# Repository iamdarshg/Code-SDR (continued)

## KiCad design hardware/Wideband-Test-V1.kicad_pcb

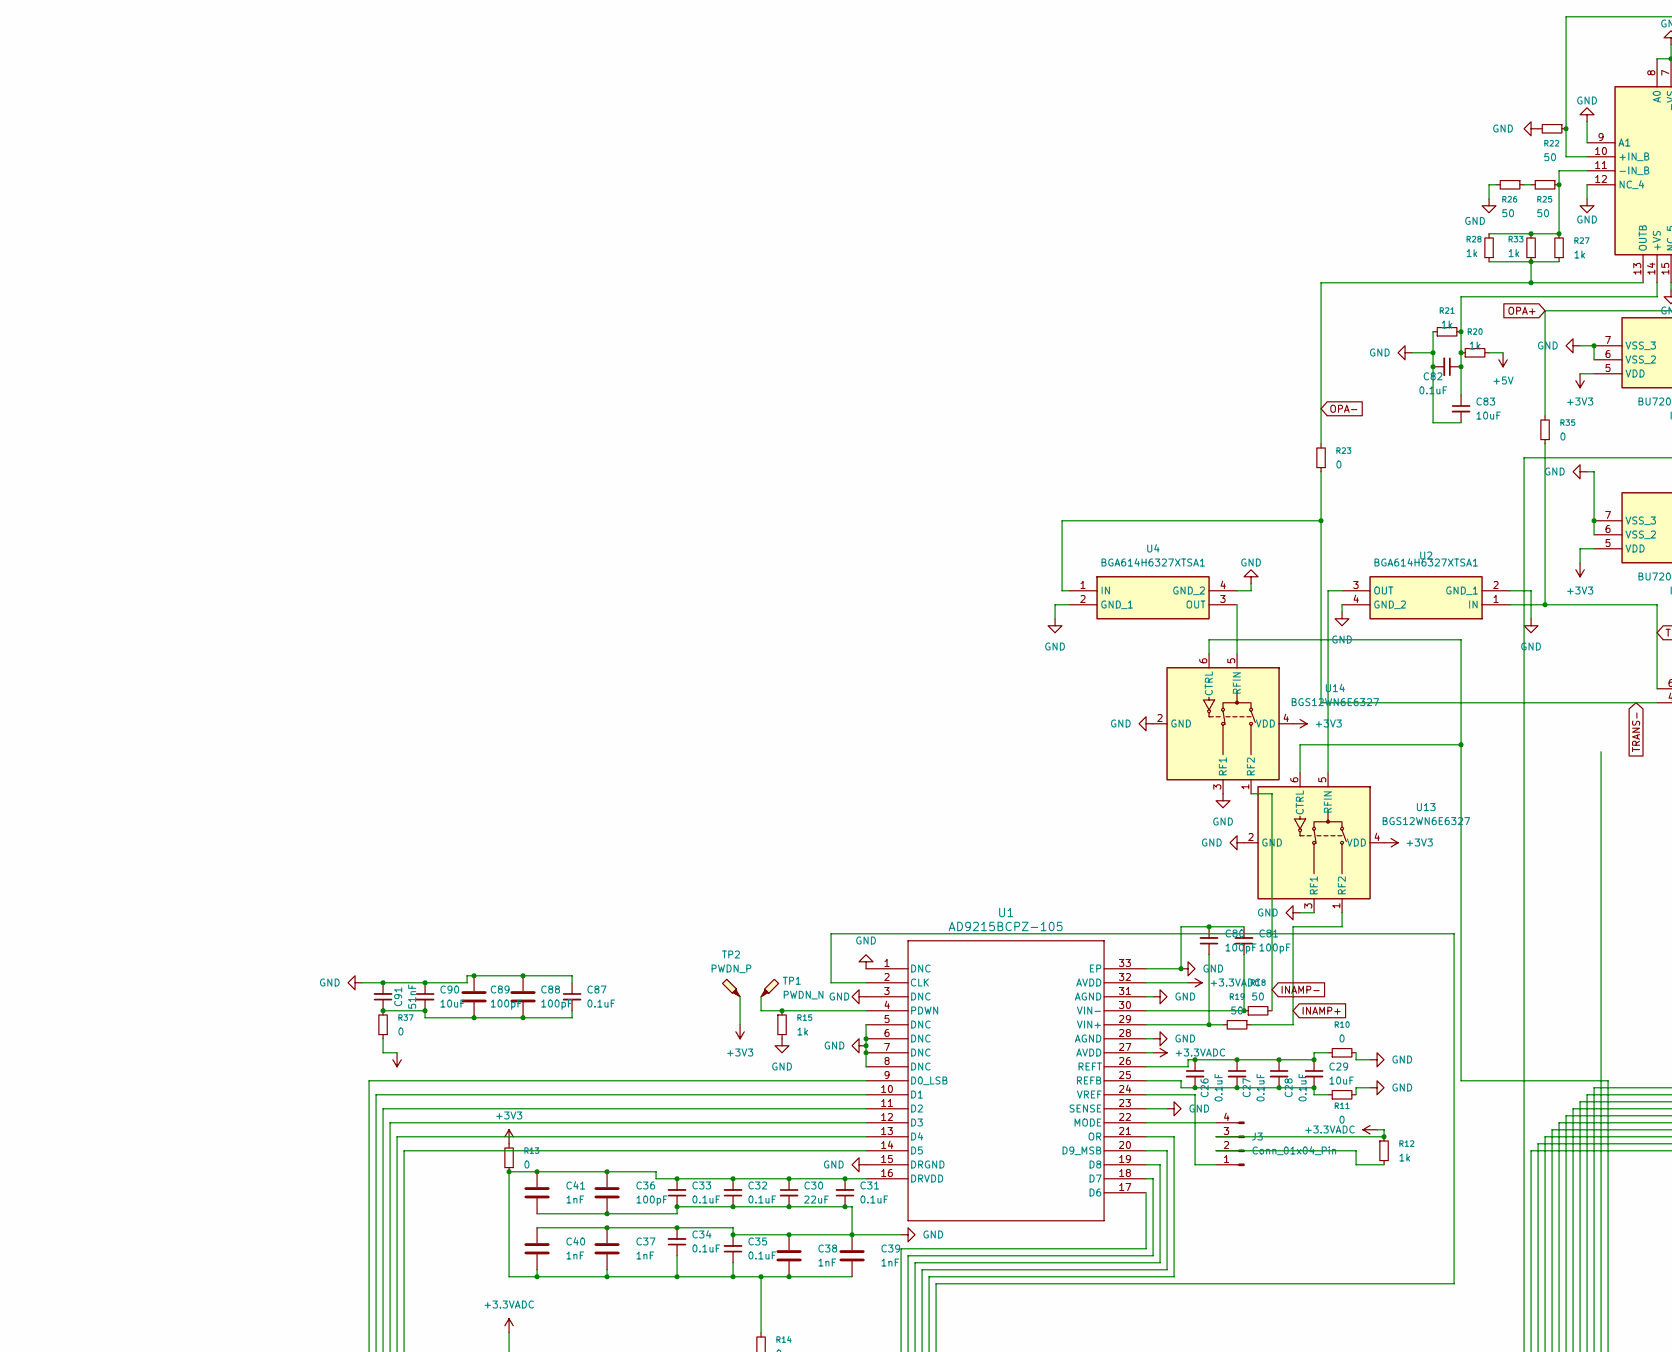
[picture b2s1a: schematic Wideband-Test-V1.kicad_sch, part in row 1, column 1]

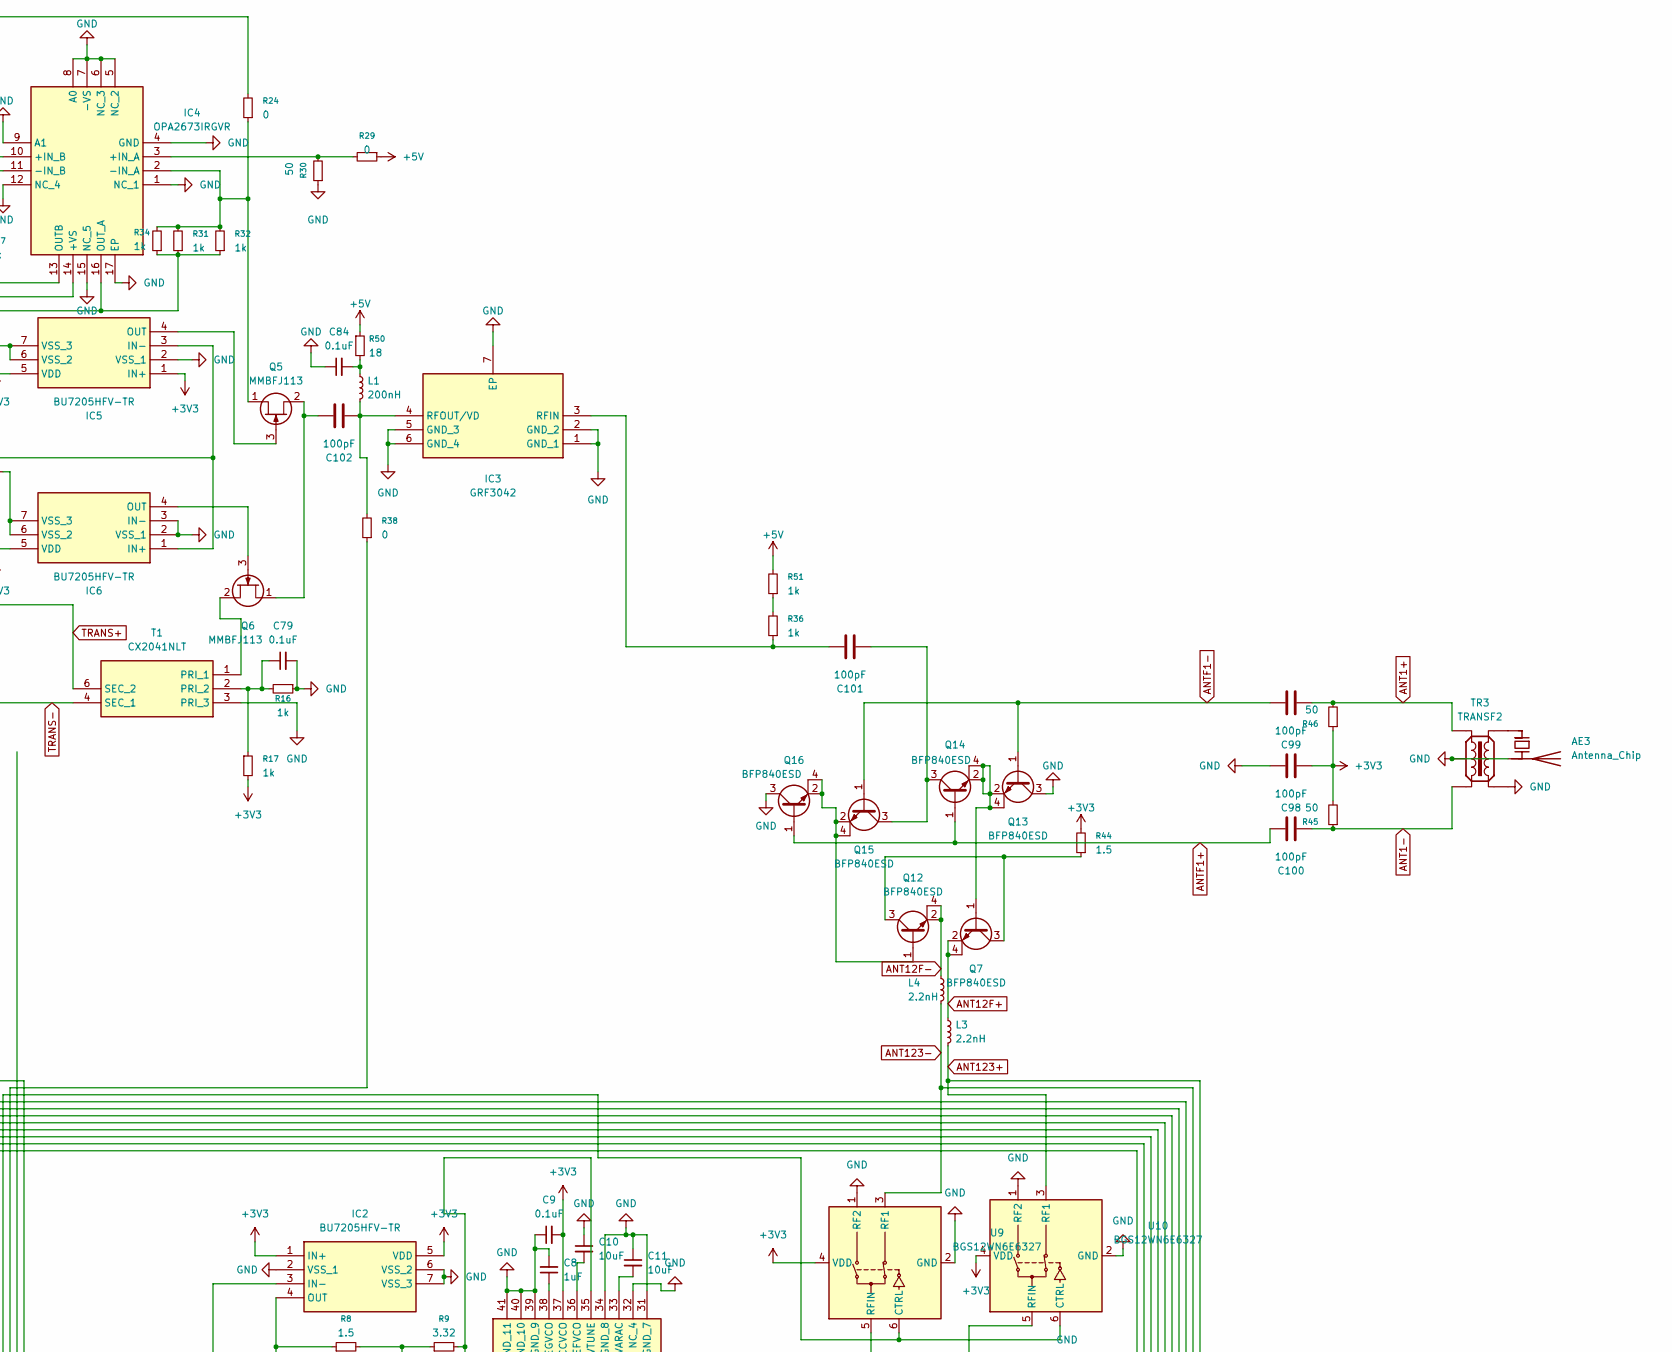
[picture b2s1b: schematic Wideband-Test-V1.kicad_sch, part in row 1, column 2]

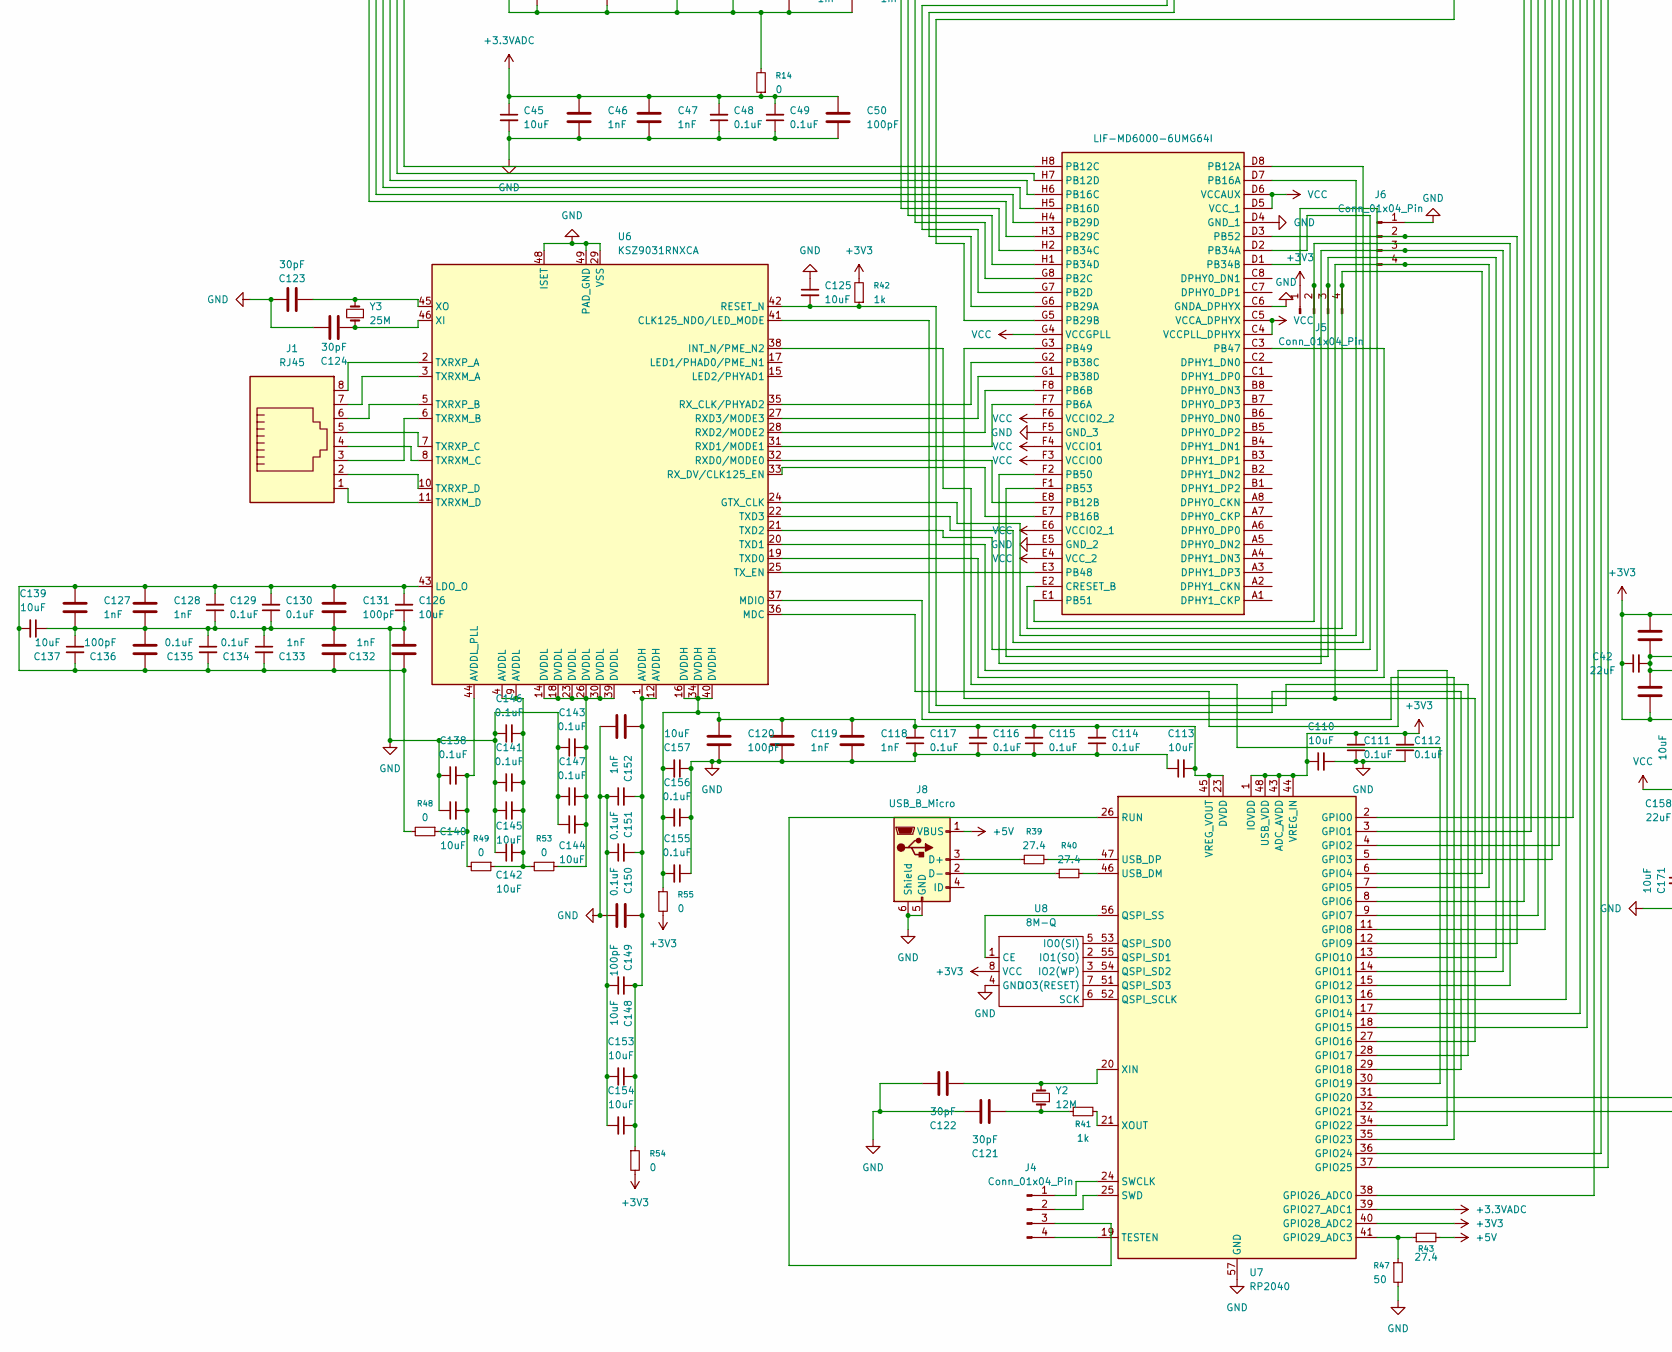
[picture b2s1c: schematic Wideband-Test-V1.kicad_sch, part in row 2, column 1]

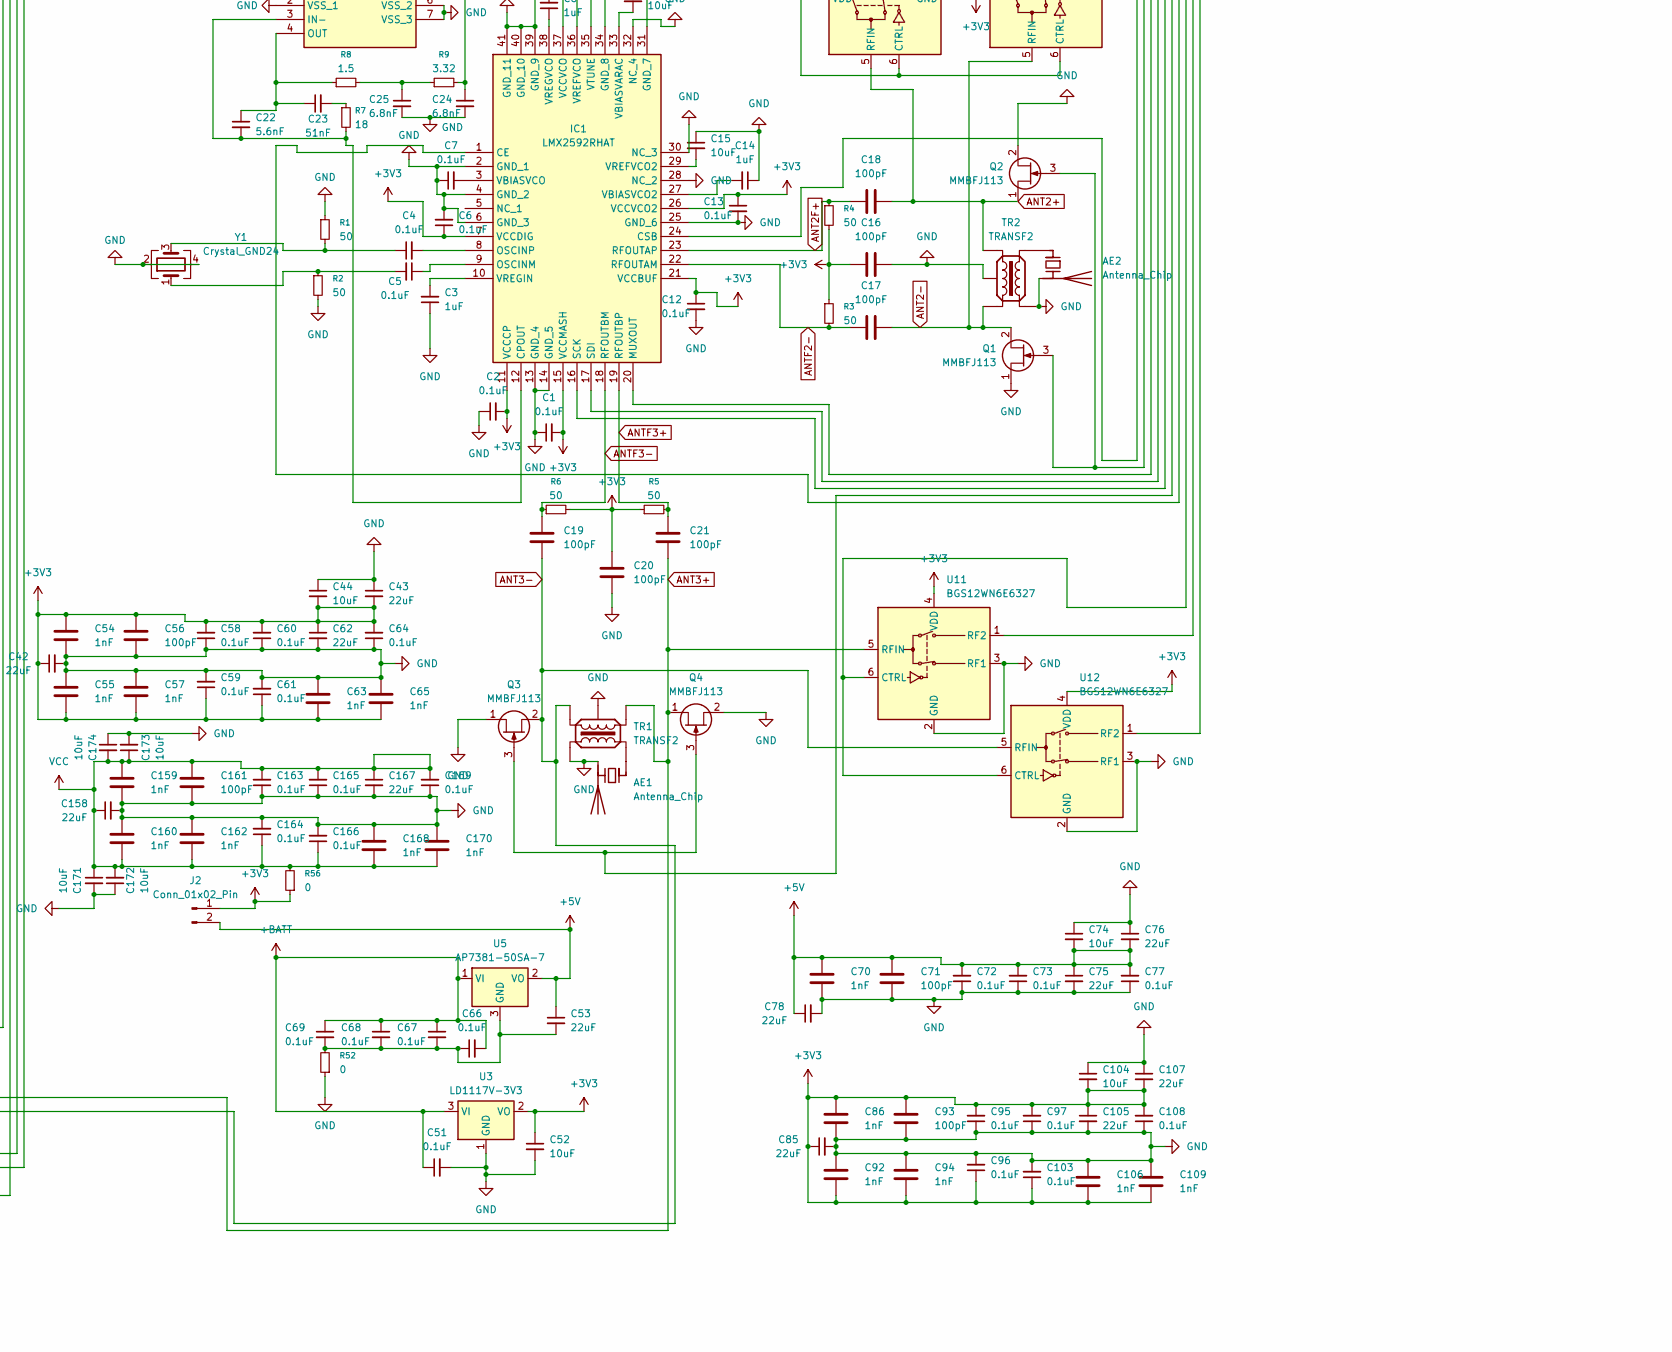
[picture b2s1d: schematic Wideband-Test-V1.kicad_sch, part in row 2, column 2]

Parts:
AE1, AE2, AE3: Antenna_Chip; SMA_Molex_73251-2200_Horizontal
C1, C2, C4, C5, C6, C7, C9, C12, C13, C26, C27, C28, C31, C32, C33, C34, C35, C48, C49, C51, C58, C59, C60, C61, C64, C66, C67, C68, C69, C72, C73, C77, C79, C82, C84, C87, C95, C96, C97, C103, C108, C111, C112, C114, C115, C116, C117, C129, C130, C134, C135, C138, C141, C143, C146, C147, C150, C151, C155, C156, C163, C164, C165, C166, C169: 0.1uF; C_0603_1608Metric
C3, C8, C14: 1uF; C_0805_2012Metric
C10, C11, C15, C29, C44, C45, C52, C74, C83, C90, C104, C110, C113, C125, C126, C137, C139, C140, C142, C144, C145, C148, C153, C154, C157, C171, C172, C173, C174: 10uF; C_0603_1608Metric
C16, C17, C18, C19, C20, C21, C36, C50, C56, C71, C88, C89, C93, C98, C99, C100, C101, C102, C120, C131, C136, C149, C161: 100pF; C_0603_1608Metric
C22: 5.6nF; C_0402_1005Metric
C23, C91: 51nF; C_1206_3216Metric
C24, C25: 6.8nF; C_0402_1005Metric
C30, C42, C43, C53, C62, C75, C76, C78, C85, C105, C107, C158, C167: 22uF; C_1206_3216Metric
C37, C38, C39, C40, C41, C46, C47, C54, C55, C57, C63, C65, C70, C86, C92, C94, C106, C109, C118, C119, C127, C128, C132, C133, C152, C159, C160, C162, C168, C170: 1nF; C_0402_1005Metric
C80, C81: 100pF; C_0402_1005Metric
C121, C122, C123, C124: 30pF; C_0603_1608Metric
IC1: LMX2592RHAT; VQFN-40-1EP_6x6mm_P0.5mm_EP3.5x3.5mm_ThermalVias; Manufacturer_Part_Number LMX2592RHAT; Mouser Part Number 595-LMX2592RHAT
IC2, IC5, IC6: BU7205HFV-TR; HVSOF5; Manufacturer_Part_Number BU7205HFV-TR; Mouser Part Number 755-BU7205HFV-TR
IC3: GRF3042; Renesas_DFN-6_1.5x1.6mm_P0.5mm; Manufacturer_Part_Number GRF3042; Mouser Part Number 459-GRF3042
IC4: OPA2673IRGVR; QFN-16-1EP_4x4mm_P0.65mm_EP2.1x2.1mm_ThermalVias; Manufacturer_Part_Number OPA2673IRGVR; Mouser Part Number 595-OPA2673IRGVR
IC7: LIF-MD6000-6UMG64I; BGA64C40P8X8_350X350X100; Manufacturer_Part_Number LIF-MD6000-6UMG64I; Mouser Part Number 842-LIFMD60006UMG64I
J1: RJ45; RJ45_Amphenol_54602-x08_Horizontal
J2: Conn_01x02_Pin; JWT_A3963_1x02_P3.96mm_Vertical
J3: Conn_01x04_Pin; Molex_Micro-Fit_3.0_43045-0412_2x02_P3.00mm_Vertical
J4, J5, J6: Conn_01x04_Pin; PinHeader_1x04_P2.54mm_Vertical
J8: USB_B_Micro; USB_Micro-B_Amphenol_10118193-0001LF_Horizontal
L1: 200nH; L_0402_1005Metric
L3, L4: 2.2nH; L_0603_1608Metric
Q1, Q2, Q3, Q4, Q5, Q6: MMBFJ113; Diodes_DFN1006-3
Q7, Q12, Q13, Q14, Q15, Q16: BFP840ESD; SOT-343_SC-70-4
R1, R2, R3, R4, R5, R6, R18, R19, R22, R25, R26, R30, R45, R46, R47: 50; R_0201_0603Metric
R7, R50: 18; R_0805_2012Metric
R8, R44: 1.5; R_0603_1608Metric
R9: 3.32; R_0603_1608Metric
R10, R11, R13, R14, R23, R24, R29, R35, R37, R38, R48, R49, R52, R53, R54, R55, R56: 0; R_0603_1608Metric
R12, R15, R16, R17, R20, R21, R27, R28, R31, R32, R33, R34, R36, R41, R42, R51: 1k; R_0805_2012Metric
R39, R40, R43: 27.4; R_0402_1005Metric
T1: CX2041NLT; Filter_SAW-6_3.8x3.8mm; Manufacturer_Part_Number CX2041NLT; Mouser Part Number 673-CX2041NLT
TP1: PWDN_N; PinHeader_1x01_P2.54mm_Vertical
TP2: PWDN_P; PinHeader_1x01_P2.54mm_Vertical
TR1, TR2, TR3: TRANSF2; MABA011108
U1: AD9215BCPZ-105; LFCSP-32-1EP_5x5mm_P0.5mm_EP3.6x3.6mm_ThermalVias
U2, U4: BGA614H6327XTSA1; SOT-343_SC-70-4; Manufacturer_Part_Number BGA614H6327XTSA1; Mouser Part Number 726-BGA614H6327XTSA1
U3: LD1117V-3V3; TO-220-3_Vertical
U5: AP7381-50SA-7; SOT-23
U6: KSZ9031RNXCA; QFN-48-1EP_7x7mm_P0.5mm_EP5.15x5.15mm_ThermalVias
U7: RP2040; QFN-56-1EP_7x7mm_P0.4mm_EP3.2x3.2mm_ThermalVias
U8: 8M-Q; SOIC-8_5.3x5.3mm_P1.27mm
U9, U10, U11, U12, U13, U14: BGS12WN6E6327; Infineon_PG-TSNP-6-10_0.7x1.1mm_0.7x1.1mm_P0.4mm
Y1: Crystal_GND24; Crystal_SMD_2520-4Pin_2.5x2.0mm
Y2: 12M; Crystal_SMD_HC49-SD
Y3: 25M; Crystal_SMD_HC49-SD

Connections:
+3.3VADC: C45.1, C46.2, C47.2, C48.2, C49.2, C50.2, J3.3, R12.1, R14.1, R37.1, U1.27 (AVDD), U1.32 (AVDD), U7.39 (GPIO27_ADC1)
+3V3: C1.2, C2.2, C6.1, C9.2, C12.1, C13.1, C16.1, C20.2, C42.1, C43.2, C44.2, C52.1, C54.2, C55.1, C56.2, C57.1, C58.2, C59.1, C60.2, C61.1, C62.1, C63.1, C64.2, C65.1, C85.1, C86.2, C92.1, C93.2, C94.1, C95.2, C96.1, C97.2, C98.1, C103.1, C104.2, C105.1, C106.1, C107.2, C108.2, C109.1, C110.1, C111.2, C112.2, IC1.7 (VCCDIG), IC1.11 (VCCCP), IC1.15 (VCCMASH), IC1.21 (VCCBUF), IC1.26 (VCCVCO2), IC1.37 (VCCVCO), IC2.1 (IN+), IC2.5 (VDD), IC5.1 (IN+), IC5.5 (VDD), IC6.5 (VDD), J2.1, J5.1, R3.1, R4.2, R5.1, R6.2, R13.2, R17.2, R42.2, R44.2, R45.2, R46.1, R54.2, R55.2, R56.1, TP2.1, U3.2 (VO), U7.1 (IOVDD), U7.10 (IOVDD), U7.22 (IOVDD), U7.33 (IOVDD), U7.40 (GPIO28_ADC2), U7.42 (IOVDD), U7.43 (ADC_AVDD), U7.44 (VREG_IN), U7.48 (USB_VDD), U7.49 (IOVDD), U8.8 (VCC), U9.4 (VDD), U10.4 (VDD), U11.4 (VDD), U12.4 (VDD), U13.4 (VDD), U14.4 (VDD)
+5V: C53.1, C70.2, C71.2, C72.2, C73.2, C74.2, C75.1, C76.2, C77.2, C78.1, J2.2, J8.1 (VBUS), R20.2, R29.1, R43.2, R50.1, R51.2, U5.2 (VO)
+BATT: C51.1, C66.2, C67.1, C68.1, C69.1, U3.3 (VI), U5.1 (VI)
ANT1+: C99.1, R46.2, TR3.5
ANT1-: C100.1, R45.1, TR3.4
ANT2+: C18.2, Q2.1 (D), TR2.5, U9.5 (RFIN)
ANT2-: C17.2, Q1.2 (S), TR2.4, U10.5 (RFIN)
ANT2F+: C18.1, IC1.23 (RFOUTAP), R4.1
ANT3+: C21.1, Q4.1 (D), TR1.5, U7.31 (GPIO20), U11.5 (RFIN)
ANT3-: C19.1, Q3.2 (S), TR1.4, U7.32 (GPIO21), U12.5 (RFIN)
ANT12F+: L3.1, Q7.2 (E), Q7.4 (E)
ANT12F-: L4.1, Q12.2 (E), Q12.4 (E)
ANT123+: L3.2, U10.3 (RF1), U12.1 (RF2)
ANT123-: L4.2, U9.3 (RF1), U11.1 (RF2)
ANTF1+: C100.2, Q14.1 (B), Q16.1 (B)
ANTF1-: C99.2, Q13.1 (B), Q15.1 (B)
ANTF2-: C17.1, IC1.22 (RFOUTAM), R3.2
ANTF3+: C21.2, IC1.19 (RFOUTBP), R5.2
ANTF3-: C19.2, IC1.18 (RFOUTBM), R6.1
GND: AE1.2 (PCB_Trace), AE2.2 (PCB_Trace), AE3.2 (PCB_Trace), C1.1, C2.1, C3.1, C6.2, C7.1, C8.2, C9.1, C10.1, C11.1, C12.2, C13.2, C14.1, C15.1, C16.2, C20.1, C24.2, C25.2, C30.2, C31.1, C32.1, C33.1, C34.2, C35.2, C36.1, C37.2, C38.2, C39.2, C40.2, C41.1, C42.2, C43.1, C44.1, C45.2, C46.1, C47.1, C48.1, C49.1, C50.1, C51.2, C52.2, C54.1, C55.2, C56.1, C57.2, C58.1, C59.2, C60.1, C61.2, C62.2, C63.2, C64.1, C65.2, C70.1, C71.1, C72.1, C73.1, C74.1, C75.2, C76.1, C77.1, C78.2, C79.2, C80.2, C81.2, C82.2, C83.2, C84.1, C85.2, C86.1, C87.1, C88.2, C89.2, C90.1, C91.2, C92.2, C93.1, C94.2, C95.1, C96.2, C97.1, C98.2, C103.2, C104.1, C105.2, C106.2, C107.1, C108.1, C109.2, C110.2, C111.1, C112.1, C113.1, C114.1, C115.1, C116.1, C117.1, C118.1, C119.1, C120.1, C121.2, C122.2, C123.2, C124.2, C125.1, C126.1, C127.1, C128.1, C129.1, C130.1, C131.1, C132.1, C133.1, C134.1, C135.1, C136.1, C137.1, C138.1, C139.1, C140.1, C141.1, C142.1, C143.1, C144.1, C145.1, C146.1, C147.1, C148.1, C149.1, C150.1, C151.1, C152.1, C153.2, C154.2, C155.1, C156.1, C157.1, C158.2, C159.1, C160.2, C161.1, C162.2, C163.1, C164.2, C165.1, C166.2, C167.2, C168.2, C169.1, C170.2, C171.2, C172.1, C173.2, C174.1, IC1.2 (GND_1), IC1.4 (GND_2), IC1.6 (GND_3), IC1.13 (GND_4), IC1.14 (GND_5), IC1.25 (GND_6), IC1.28 (NC_2), IC1.30 (NC_3), IC1.31 (GND_7), IC1.32 (NC_4), IC1.34 (GND_8), IC1.39 (GND_9), IC1.40 (GND_10), IC1.41 (GND_11), IC2.2 (VSS_1), IC2.6 (VSS_2), IC2.7 (VSS_3), IC3.1 (GND_1), IC3.2 (GND_2), IC3.5 (GND_3), IC3.6 (GND_4), IC3.7 (EP), IC4.1 (NC_1), IC4.4 (GND), IC4.5 (NC_2), IC4.6 (NC_3), IC4.7 (-VS), IC4.8 (A0), IC4.9 (A1), IC4.12 (NC_4), IC4.15 (NC_5), IC4.17 (EP), IC5.2 (VSS_1), IC5.6 (VSS_2), IC5.7 (VSS_3), IC6.2 (VSS_1), IC6.3 (IN-), IC6.6 (VSS_2), IC6.7 (VSS_3), IC7.C6 (GNDA_DPHYX), IC7.D4 (GND_1), IC7.E5 (GND_2), IC7.F5 (GND_3), J6.1, J8.5 (GND), J8.6 (Shield), Q1.1 (D), Q2.2 (S), Q3.1 (D), Q4.2 (S), Q13.3 (C), Q16.3 (C), R1.1, R2.2, R10.2, R11.2, R15.2, R16.1, R21.1, R22.2, R26.2, R30.1, R47.2, R52.1, T1.3 (PRI_3), TR1.1,6, TR1.2, TR2.1,6, TR2.2, TR3.1,6, TR3.2, U1.1 (DNC), U1.3 (DNC), U1.5 (DNC), U1.6 (DNC), U1.7 (DNC), U1.8 (DNC), U1.15 (DRGND), U1.23 (SENSE), U1.28 (AGND), U1.31 (AGND), U1.33 (EP), U2.2 (GND_1), U2.4 (GND_2), U3.1 (GND), U4.2 (GND_1), U4.4 (GND_2), U6.29 (VSS), U6.48 (ISET), U6.49 (PAD_GND), U7.57 (GND), U8.4 (GND), U9.1 (RF2), U9.2 (GND), U10.1 (RF2), U10.2 (GND), U11.2 (GND), U11.3 (RF1), U12.2 (GND), U12.3 (RF1), U13.2 (GND), U13.3 (RF1), U14.2 (GND), U14.3 (RF1), Y1.2, Y1.4
INAMP+: R19.1, U13.1 (RF2)
INAMP-: R18.2, U14.1 (RF2)
unnamed: AE1.1 (FEED), TR1.3
unnamed: AE2.1 (FEED), TR2.3
unnamed: AE3.1 (FEED), TR3.3
unnamed: C4.1, R1.2, Y1.3
unnamed: C5.2, R2.1, Y1.1
unnamed: C23.2, R7.1
unnamed: C25.1, R8.2, R9.1
unnamed: C84.2, L1.1, R50.2
unnamed: C87.2, C88.1, C89.1, C90.2, C91.1, R37.2
unnamed: C121.1, R41.1, Y2.1
unnamed: C141.2, C142.2, C145.2, C146.2, R49.1, R53.2, U6.4 (AVDDL), U6.9 (AVDDL)
unnamed: C143.2, C144.2, C147.2, R53.1, U6.14 (DVDDL), U6.18 (DVDDL), U6.23 (DVDDL), U6.26 (DVDDL), U6.30 (DVDDL), U6.39 (DVDDL)
unnamed: C148.2, C149.2, C150.2, C151.2, C152.2, C153.1, C154.1, R54.1, U6.1 (AVDDH), U6.12 (AVDDH)
unnamed: IC1.1 (CE), U7.2 (GPIO0)
unnamed: C22.2, IC1.12 (CPOUT), IC2.3 (IN-), R7.2
unnamed: IC1.24 (CSB), U7.3 (GPIO1)
unnamed: IC1.20 (MUXOUT), U7.11 (GPIO8)
unnamed: C5.1, IC1.9 (OSCINM)
unnamed: C4.2, IC1.8 (OSCINP)
unnamed: IC1.16 (SCK), U7.4 (GPIO2)
unnamed: IC1.17 (SDI), U7.5 (GPIO3)
unnamed: C11.2, IC1.33 (VBIASVARAC)
unnamed: C14.2, IC1.27 (VBIASVCO2)
unnamed: C7.2, IC1.3 (VBIASVCO)
unnamed: C15.2, IC1.29 (VREFVCO2)
unnamed: C10.2, IC1.36 (VREFVCO)
unnamed: C3.2, IC1.10 (VREGIN)
unnamed: C8.1, IC1.38 (VREGVCO)
unnamed: C24.1, IC1.35 (VTUNE), R9.2
unnamed: C22.1, C23.1, IC2.4 (OUT), R8.1
unnamed: C101.2, IC3.3 (RFIN), R36.1
unnamed: C102.1, IC3.4 (RFOUT/VD), L1.2, R38.2
unnamed: IC4.3 (+IN_A), R29.2, R30.2
unnamed: IC4.10 (+IN_B), R22.1, R24.2
unnamed: C82.1, C83.1, IC4.14 (+VS), R20.1, R21.2
unnamed: IC4.2 (-IN_A), Q5.1 (D), R24.1, R31.2, R32.2, R34.2
unnamed: IC4.11 (-IN_B), R25.1, R27.2, R28.2, R33.2
unnamed: IC5.3 (IN-), IC6.1 (IN+), U7.8 (GPIO6)
unnamed: IC5.4 (OUT), Q5.3 (G)
unnamed: IC6.4 (OUT), Q6.3 (G)
unnamed: IC7.E2 (CRESET_B), J5.4, U7.6 (GPIO4)
unnamed: IC7.G8 (PB2C), U1.19 (D8)
unnamed: IC7.G7 (PB2D), U1.20 (D9_MSB)
unnamed: IC7.F7 (PB6A), U6.31 (RXD1/MODE1)
unnamed: IC7.F8 (PB6B), U6.28 (RXD2/MODE2)
unnamed: IC7.D8 (PB12A), U6.22 (TXD3)
unnamed: IC7.E8 (PB12B), U6.32 (RXD0/MODE0)
unnamed: IC7.H8 (PB12C), U1.14 (D5)
unnamed: IC7.H7 (PB12D), U1.13 (D4)
unnamed: IC7.D7 (PB16A), U6.24 (GTX_CLK)
unnamed: IC7.E7 (PB16B), U6.33 (RX_DV/CLK125_EN)
unnamed: IC7.H6 (PB16C), U1.12 (D3)
unnamed: IC7.H5 (PB16D), U1.11 (D2)
unnamed: IC7.G6 (PB29A), U1.21 (OR)
unnamed: IC7.G5 (PB29B), U1.2 (CLK)
unnamed: IC7.H3 (PB29C), U1.9 (D0_LSB)
unnamed: IC7.H4 (PB29D), U1.10 (D1)
unnamed: IC7.D2 (PB34A), U6.21 (TXD2)
unnamed: IC7.D1 (PB34B), U6.20 (TXD1)
unnamed: IC7.H2 (PB34C), U1.17 (D6)
unnamed: IC7.H1 (PB34D), U1.18 (D7)
unnamed: IC7.G2 (PB38C), U6.35 (RX_CLK/PHYAD2)
unnamed: IC7.G1 (PB38D), U6.27 (RXD3/MODE3)
unnamed: IC7.C3 (PB47), U6.19 (TXD0)
unnamed: IC7.E3 (PB48), U6.25 (TX_EN)
unnamed: IC7.G3 (PB49), J6.4, U7.7 (GPIO5), U7.27 (GPIO16)
unnamed: IC7.F2 (PB50), J6.3, U7.14 (GPIO11)
unnamed: IC7.E1 (PB51), J5.2, U7.15 (GPIO12)
unnamed: IC7.D3 (PB52), J6.2, U7.12 (GPIO9)
unnamed: IC7.F1 (PB53), J5.3, U7.13 (GPIO10)
unnamed: J3.1, U1.24 (VREF)
unnamed: J3.2, R12.2
unnamed: J3.4, U1.22 (MODE)
unnamed: J4.1, U7.24 (SWCLK)
unnamed: J4.2, U7.25 (SWD)
unnamed: J4.3, U7.26 (RUN)
unnamed: J4.4, U7.19 (TESTEN)
unnamed: J8.3 (D+), R39.1
unnamed: J8.2 (D-), R40.1
unnamed: Q1.3 (G), Q2.3 (G), U7.9 (GPIO7)
unnamed: Q3.3 (G), Q4.3 (G), U7.16 (GPIO13)
unnamed: C102.2, Q5.2 (S), Q6.1 (D)
unnamed: Q6.2 (S), T1.1 (PRI_1)
unnamed: Q7.1 (B), Q13.2 (E), Q13.4 (E), Q14.2 (E), Q14.4 (E)
unnamed: Q12.1 (B), Q15.2 (E), Q15.4 (E), Q16.2 (E), Q16.4 (E)
unnamed: Q7.3 (C), Q12.3 (C), R44.1
unnamed: C101.1, Q14.3 (C), Q15.3 (C)
unnamed: R25.2, R26.1
unnamed: R36.2, R51.1
unnamed: C79.1, R16.2, R17.1, T1.2 (PRI_2)
unnamed: C30.1, C31.2, C32.2, C33.2, C34.1, C35.1, C36.2, C37.1, C38.1, C39.1, C40.1, C41.2, R13.1, R14.2, U1.16 (DRVDD)
unnamed: R15.1, TP1.1, U1.4 (PDWN)
unnamed: C26.2, C27.2, C28.2, C29.2, R11.1, U1.25 (REFB)
unnamed: C26.1, C27.1, C28.1, C29.1, R10.1, U1.26 (REFT)
unnamed: C80.1, R19.2, U1.29 (VIN+)
unnamed: C81.1, R18.1, U1.30 (VIN-)
unnamed: C53.2, C66.1, C67.2, C68.2, C69.2, R52.2, U5.3 (GND)
unnamed: C138.2, C140.2, R48.1, R49.2, U6.44 (AVDDL_PLL)
unnamed: U6.41 (CLK125_NDO/LED_MODE), U7.29 (GPIO18)
unnamed: U6.38 (INT_N/PME_N2), U7.30 (GPIO19)
unnamed: C126.2, C127.2, C128.2, C129.2, C130.2, C131.2, C132.2, C133.2, C134.2, C135.2, C136.2, C137.2, C139.2, R48.2, U6.43 (LDO_O)
unnamed: U6.36 (MDC), U7.34 (GPIO22)
unnamed: U6.37 (MDIO), U7.35 (GPIO23)
unnamed: C125.2, R42.1, U6.42 (RESET_N), U7.28 (GPIO17)
unnamed: J1.7, U6.3 (TXRXM_A)
unnamed: J1.3, U6.6 (TXRXM_B)
unnamed: J1.4, U6.8 (TXRXM_C)
unnamed: J1.1, U6.11 (TXRXM_D)
unnamed: J1.8, U6.2 (TXRXP_A)
unnamed: J1.6, U6.5 (TXRXP_B)
unnamed: J1.5, U6.7 (TXRXP_C)
unnamed: J1.2, U6.10 (TXRXP_D)
unnamed: C124.1, U6.46 (XI), Y3.1
unnamed: C123.1, U6.45 (XO), Y3.2
unnamed: R38.1, U7.38 (GPIO26_ADC0)
unnamed: R43.1, R47.1, U7.41 (GPIO29_ADC3)
unnamed: U7.52 (QSPI_SCLK), U8.6 (SCK)
unnamed: U7.53 (QSPI_SD0), U8.5 (IO0(SI))
unnamed: U7.55 (QSPI_SD1), U8.2 (IO1(SO))
unnamed: U7.54 (QSPI_SD2), U8.3 (IO2(WP))
unnamed: U7.51 (QSPI_SD3), U8.7 (IO3(RESET))
unnamed: U7.56 (QSPI_SS), U8.1 (CE)
unnamed: R40.2, U7.46 (USB_DM)
unnamed: R39.2, U7.47 (USB_DP)
unnamed: C113.2, C114.2, C115.2, C116.2, C117.2, C118.2, C119.2, C120.2, C155.2, C156.2, C157.2, R55.1, U6.16 (DVDDH), U6.34 (DVDDH), U6.40 (DVDDH), U7.23 (DVDD), U7.45 (VREG_VOUT), U7.50 (DVDD)
unnamed: C122.1, U7.20 (XIN), Y2.2
unnamed: R41.2, U7.21 (XOUT)
unnamed: U7.18 (GPIO15), U9.6 (CTRL), U10.6 (CTRL)
unnamed: U7.17 (GPIO14), U11.6 (CTRL), U12.6 (CTRL)
unnamed: U7.37 (GPIO25), U13.6 (CTRL), U14.6 (CTRL)
unnamed: U2.3 (OUT), U13.5 (RFIN)
unnamed: U4.3 (OUT), U14.5 (RFIN)
OPA+: IC4.16 (OUT_A), R31.1, R32.1, R34.1, R35.2
OPA-: IC4.13 (OUTB), R23.2, R27.1, R28.1, R33.1
TRANS+: R35.1, T1.6 (SEC_2), U2.1 (IN)
TRANS-: R23.1, T1.4 (SEC_1), U4.1 (IN)
VCC: C158.1, C159.2, C160.1, C161.2, C162.1, C163.2, C164.1, C165.2, C166.1, C167.1, C168.1, C169.2, C170.1, C171.1, C172.2, C173.1, C174.2, IC7.C4 (VCCPLL_DPHYX), IC7.C5 (VCCA_DPHYX), IC7.D5 (VCC_1), IC7.D6 (VCCAUX), IC7.E4 (VCC_2), IC7.E6 (VCCIO2_1), IC7.F3 (VCCIO0), IC7.F4 (VCCIO1), IC7.F6 (VCCIO2_2), IC7.G4 (VCCGPLL), R56.2

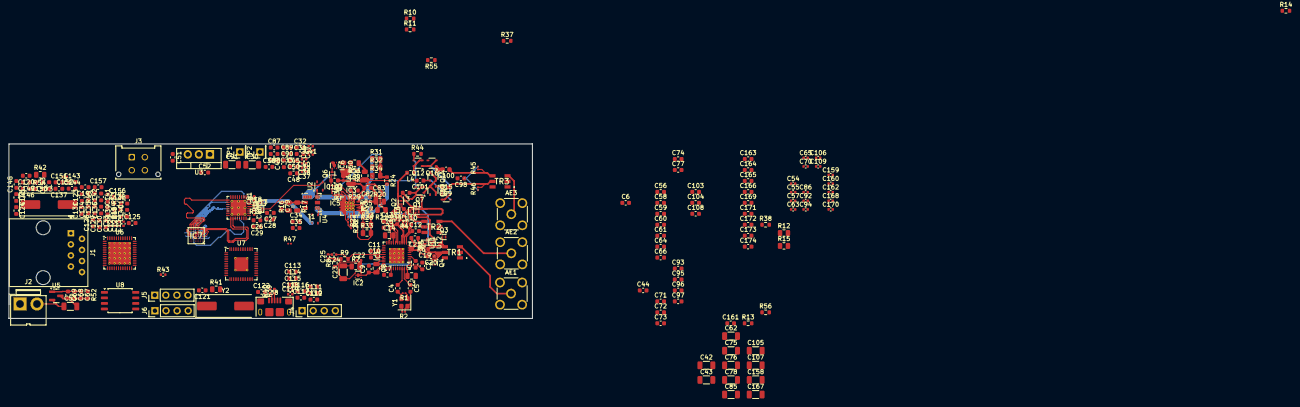
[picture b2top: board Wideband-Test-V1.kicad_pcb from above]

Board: 4 copper layers, 120.0 x 40.0 mm, 285 parts (0 on the bottom side), 160 nets.

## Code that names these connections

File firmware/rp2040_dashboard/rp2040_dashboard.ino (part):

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// the SPI bus, the telemetry register file, and the PHY identity.
static void selftest(void) {
    // 1. FPGA configured?
    if (digitalRead(PIN_FPGA_CDONE) != HIGH) {
        Serial.println("# SELFTEST: FPGA CDONE low - not configured");
        fault_raise(FAULT_FPGA_CONFIG);
    }
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}

// ---------------------------------------------------------------- pin mapping
#define PIN_FPGA_SCK   2    // FPGA_SPI_SCK_MCU  U10.2
#define PIN_FPGA_MOSI  3    // FPGA_SPI_MOSI     U10.3
#define PIN_FPGA_MISO  4    // FPGA_SPI_MISO     U10.4
#define PIN_FPGA_CS_N  5    // FPGA_SPI_CS_N     U10.5
#define PIN_FPGA_RESET 29   // FPGA_RESET_N      U10.29
#define PIN_FPGA_CDONE 41   // FPGA_CDONE        U10.41
// ------------------------------------------------------------- link constants
static const float ADC_HZ        = 100.0e6;  // REF_100M_ADC
static const int   JUMBO_MTU     = 9000;     // all datagrams are jumbo (v2_top MTU)
// 8972 B payload / 9038 B wire @ 9000 MTU
static const float UDP_CEIL_MBPS = 992.7;
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
    // Release the FPGA and wait for CDONE.
    digitalWrite(PIN_FPGA_RESET, HIGH);
    pinMode(PIN_FPGA_CDONE, INPUT);
    uint32_t t0 = millis();
    while (!digitalRead(PIN_FPGA_CDONE) && (millis() - t0) < 2000) delay(10);

    SPI.setSCK(PIN_FPGA_SCK);
    SPI.setTX(PIN_FPGA_MOSI);
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    faults_watchdog_kick();

    // FPGA configuration lost? CDONE should stay high in user mode.
    if (digitalRead(PIN_FPGA_CDONE) != HIGH) {
        fault_raise(FAULT_FPGA_CONFIG);
        Serial.println("# FPGA CDONE low - reconfiguring");
        if (g_mode == 1) fpga_select_mode(1); else fpga_select_mode(0);
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
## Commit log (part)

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2025-11-17 TODO
2025-11-18 0c i think
2025-11-23 1 and a u-turn in hardware
2025-11-25 Reorganised and cleaned up
2025-11-25 Document Virtual FPGA Simulation and Test Framework
    Added a section for Virtual FPGA Simulation and Test Framework, detailing tools, implementation requirements, and example test scripts for Verilog code verification.
2025-11-25 prompts and optimisations
2025-11-26 prompt 1 complete!
2025-11-26 so i found some issues
2025-11-26 prompt 2 complete!
2025-11-26 1A fixed, testing fixed
2025-11-28 test troubles
2025-11-28 pain.
2025-11-28 fixes i hope
2025-11-29 more fixes
2025-11-29 stuff? different ai?
2025-11-29 moving to verilator
2025-12-03 moving again to openFPGA
2025-12-09 more fixes i hope?
2026-01-15 Add MIT License to the project
2026-01-15 feat: ⚡ Bolt: Optimize DDC filter with fftconvolve
    This commit optimizes the `_apply_lowpass_filter` method in the `DigitalDownconverter` class by replacing `scipy.signal.lfilter` with `scipy.signal.fftconvolve`.
    The `lfilter` function is inefficient for long filter kernels, which are common in SDR applications. The `fftconvolve` function, which uses FFTs to perform the convolution, is significantly more perf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
    **Performance Impact:**
    - **DDC Throughput:** Increased by up to 15% in some configurations.
    - **Combined Pipeline:** Real-time factor improved from `21.81x` to `19.05x` (a 12% improvement).
    **Verification:**
2026-01-15 cleanup, removal of repeated, legacy or ununsed files
2026-01-16 ⚡ Bolt: Optimize NCO generation with stateful synchronizer
    💡 **What:** Replaced the stateless NCO signal generation in `DigitalDownconverter` with a stateful `NCOSynchronizer` class. This avoids costly recalculations of the NCO's complex exponential for ever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
    🎯 **Why:** The previous implementation was inefficient for streaming data, as it repeatedly generated the NCO signal from scratch. This caused unnecessary CPU load and introduced phase discontinuitie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
    📊 **Impact:** This change improves the NCO-only processing speed by ~10x.
    - **Previous:** ~5.5 ms per run
    - **After:** ~0.5 ms per run
    🔬 **Measurement:** The performance improvement was measured
2026-01-16 Fix: Correct import statement in tests to resolve SyntaxError
    Corrected the import statement in `tests/test_fft_ddc_performance.py` to use an underscore instead of a hyphen, matching the renamed `wideband_sdr_software` package. This resolves the `SyntaxError` t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
2026-01-16 Refactor: Improve Python packaging and fix test imports
    - Renamed `wideband-sdr-software` to `wideband_sdr_software` to create a valid Python package.
    - Added an `__init__.py` file to the `wideband_sdr_software` directory.
    - Updated the import statement in `tests/test_fft_ddc_performance.py` to use the new package name.
    - Moved the `NCOSynchronizer` class to its own file (`nco_synchronizer.py`) for better code organization.
    - Updated `digital_downconverter.py` to import `NCOSynchronizer` from its new module.
    These changes resolve the import errors that were causing the test suite to fail and improve the overall structure of the Python code.
2026-01-16 Revert: Revert incorrect directory rename and fix imports
    - Reverted the renaming of the `wideband_sdr_software` directory back to `wideband-sdr-software`.
    - Removed the `__init__.py` file from the `wideband-sdr-software` directory.
    - Updated the import in `wideband-sdr-software/digital_downconverter.py` to a direct import.
    - Restored the original `sys.path` logic in `tests/test_fft_ddc_performance.py`.
    These changes restore the original project structure and fix the import errors that were causing the CI to fail. All tests are now passing.
2026-01-17 perf: Optimize DDC filter with single complex convolution
    Replaced the two separate `fftconvolve` operations on the real and
    imaginary components of the signal with a single, more efficient
    `fftconvolve` on the complex signal.
    This optimization leverages SciPy's efficient handling of complex-valued
    arrays, reducing Python overhead and improving overall throughput.
    Performance measurements show a ~28% reduction in the DDC pipeline's
2026-01-19 feat: Explore performance optimizations
    Investigated splitting complex convolution into real and imaginary parts in `digital_downconverter.py`.
    Performance testing showed this to be a performance anti-pattern, so the change was reverted. No performance improvements were committed.
2026-01-21 I investigated an opportunity to improve the signal processing quality in the digital downconverter. While the change was correct from a signal processing perspective, it introduced a significant per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
2026-01-21 feat: Optimize DDC with oaconvolve and refactor tests
    This commit introduces a performance optimization to the Digital Downconverter (DDC) by replacing `scipy.signal.fftconvolve` with `scipy.signal.oaconvolve` for low-pass filtering. This change improve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
    The performance benchmark suite has been refactored to ensure a valid "apples-to-apples" comparison and to avoid test coverage regressions. The suite now runs the same benchmarks before and after the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
    The combined pipeline is still not performant, and further investigation is required to identify the new bottleneck.
2026-01-21 feat(testing): Add edge case tests and harden DDC
    - Adds a new test file, `tests/test_edge_cases.py`, to validate the DigitalDownconverter's behavior with invalid inputs.
    - Fixes a `ZeroDivisionError` when initializing with zero bandwidth.
    - Adds a `TypeError` for non-complex input signals.
    - Updates `.gitignore` to exclude `*.egg-info` directories.
2026-01-23 feat(testing): Overhaul Verilog and Python testing
    - Rewrites the `cic_decimator` cocotb test to use a golden model, providing a more robust and accurate verification of the Verilog module.
    - Adds a new pytest suite (`test_edge_cases.py`) for the Python `DigitalDownconverter`, including tests for invalid inputs and zero bandwidth.
    - Hardens the `DigitalDownconverter` by adding input validation to handle the new edge cases.
    - Cleans up the repository by removing generated files (performance reports, plots, simulation build artifacts) from version control.
    - Updates `.gitignore` to prevent future commits of generated files.
2026-01-25 feat: Overhaul Verilog test infrastructure with cocotb
    This commit replaces the entire Verilog test infrastructure with a new suite of `cocotb` tests. The old, brittle testbenches have been removed and replaced with a modern, Python-based framework that 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
    The new test suite includes:
    - Unit tests for `adc_interface`, `digital_downconverter`, `fft_processor`, `ethernet_mac`, and `udp_ip_stack`.
    - A top-level integration test for the `fpga_processing_pipeline` to verify the entire data flow.
    - An updated `run_all_tests.sh` script to execute the new test suite.
    - Updated documentation in `tests/README.md`.
2026-04-28 hardwares
2026-05-01 fix: implement integration testing and performance characterization (Issue 11)
    - Enhanced clock_manager.v with behavioral simulation models for multi-domain clocks (105MHz to 1.2GHz).
    - Implemented tests/cocotb_tests/test_fpga_processing_pipeline.py for end-to-end FPGA data flow verification.
    - Fixed multiple bugs in tests/test_fft_ddc_performance.py and digital_downconverter.py.
    - Improved DDC filtering performance and stability with Remez algorithm fallback.
    - Generated comprehensive verification report in ISSUE_11_VERIFICATION_REPORT.md.
    - Updated .gitignore to exclude simulation and performance artifacts.
2026-05-01 fix: overhaul RTL for elaboration cleanliness and robust integration testing
    - Added \`default_nettype none\` and explicitly declared all internal nets in top-level and core modules.
    - Replaced runtime \`generate if\` with static module instantiation and runtime enables in \`fpga_processing_pipeline.v\`.
    - Resolved multiple-driver and confused ownership hazards on configuration registers.
    - Implemented robust \`cocotb\` integration tests with hard assertions and SPI-based configuration.
    - Fixed software performance benchmark suite and improved DDC filter stability.
    - Updated documentation and verification report to reflect RTL quality and test results.
2026-05-02 fix: final RTL overhaul for Issue 11 compliance
    - Completely rewritten SPI FSM in rp2040_interface.v to fix reset and bit-width bugs.
    - Resolved 48-bit to 32-bit FFT data truncation in top-level data mux.
    - Fixed GMII clocking to maintain constant 125MHz for external PHY.
    - Updated cocotb tests with robust assertions and SPI-based config.
    - Completed dependency mapping in lint and build scripts.
    - Finalized ISSUE_11_VERIFICATION_REPORT.md with verified RTL status.
2026-05-02 fix: final RTL overhaul for Issue 11 compliance
    - Completely rewritten SPI FSM in rp2040_interface.v to fix reset and bit-width bugs.
    - Added explicit rst_n to rp2040_interface and decoupled config from pll_locked.
    - Resolved 48-bit to 32-bit FFT data truncation in top-level data mux.
    - Fixed GMII clocking to maintain constant 125MHz for external PHY compatibility.
    - Updated adc_interface tests to match current RTL port names.
    - Updated cocotb tests with robust assertions and SPI-based config.
2026-05-02 fix: finalize RTL for Issue 11 with syntax and lint fixes
    - Fixed syntax error in fpga_processing_pipeline.v (missing comma in rp2040_interface instantiation).
    - Updated lint_output.txt with successful elaboration results.
    - Verified SPI FSM, FFT packing, and GMII clocking isolation.
    - Synchronized ADC cocotb tests with current RTL port definitions.
    - Ensured all dependencies (compensation_filter.v) are included in verification scripts.
2026-05-02 Implement build system, configuration management, and deployment procedures (Issue 12)
    This commit addresses Issue 12 by providing the necessary infrastructure for
    building, configuring, and deploying the Code-SDR system. Key changes include:
    - Automated version generation for RTL and software.
    - JSON-based configuration management with validation.
    - Master build script for FPGA synthesis preparation.
    - Flashing script template for FPGA and RP2040.
2026-05-02 Repair FPGA-local FFT receive path for sustained 105 MSPS (Issue 12)
    This commit implements a high-performance 1024-point FFT receive path
    capable of sustaining 105 MSPS. Key improvements include:
    - FFT Core: Replaced batch processor with a Radix-2 SDF architecture
    for 1 sample/clock throughput.
    - Twiddles: Implemented fixed-point rotations using deterministic
    twiddle factors generated by a new Python tool.
2026-05-04 Repair FPGA FFT receive path for sustained 105 MSPS throughput
    This patch addresses Issue #12 by replacing the unsynthesizable legacy FFT
    with a high-performance Radix-2 DIF SDF (Single-path Delay Feedback)
    architecture.
    Key Improvements:
    - Sustained 105 MSPS throughput at 105 MHz (1 sample per clock cycle).
    - Synthesizable RTL: Removed all 'real' types and behavioral math;
2026-05-05 Address issue 12 FFT receive path blockers
2026-05-05 Restore sustained FFT receive path
2026-05-05 Tighten streaming FFT receive integration
2026-05-05 Prove FFT bins and fix IPv4 checksum
2026-05-06 Fix MAC word handshake semantics
